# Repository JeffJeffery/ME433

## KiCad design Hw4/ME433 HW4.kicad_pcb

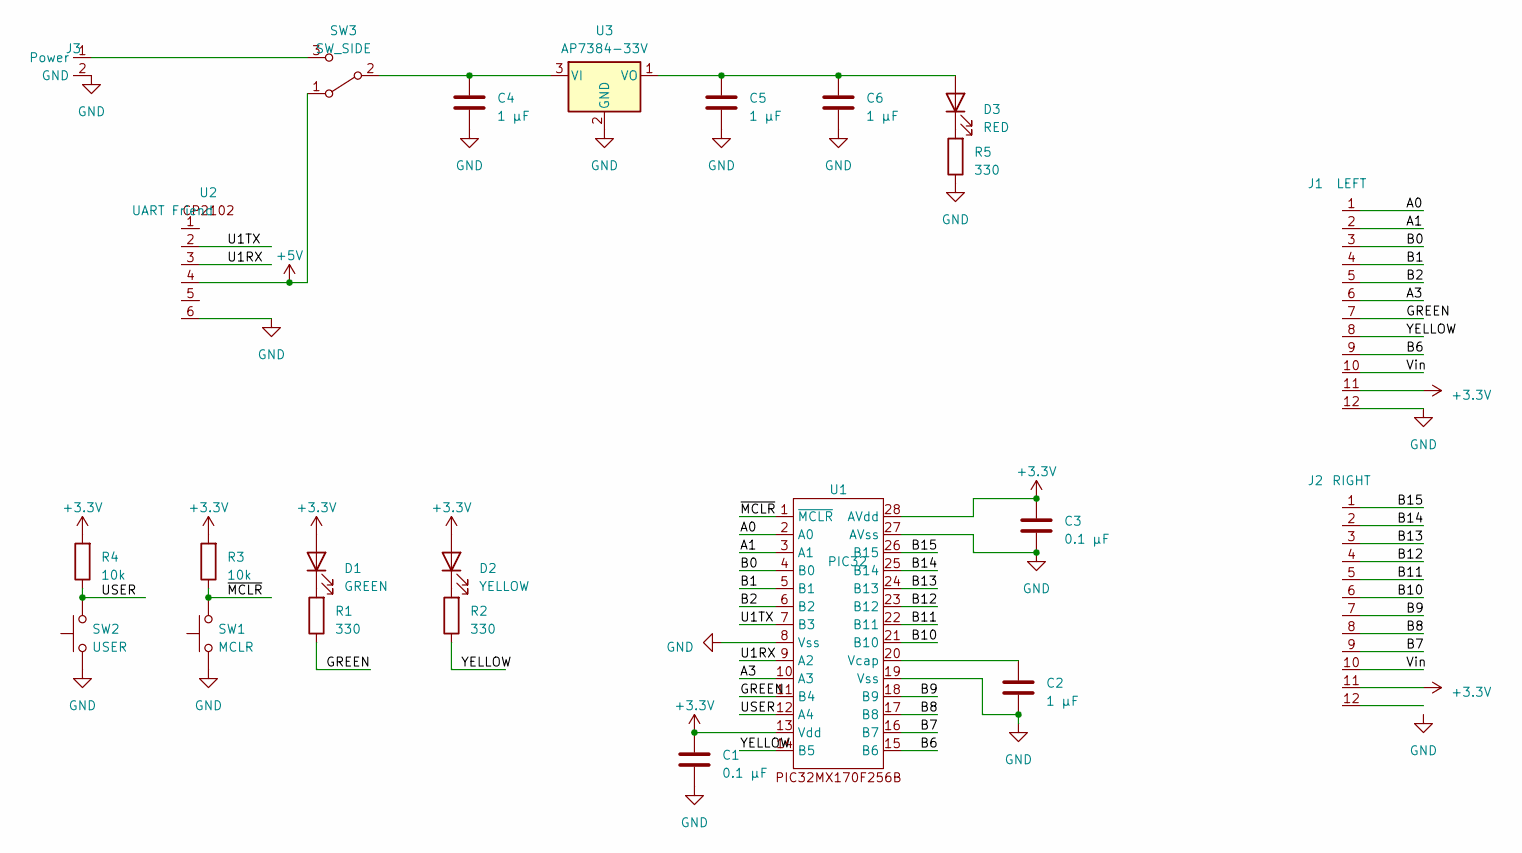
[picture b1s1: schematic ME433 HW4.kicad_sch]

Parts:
C1, C3: 0.1 µF; C_Disc_D3.4mm_W2.1mm_P2.50mm
C2, C4, C5, C6: 1 µF; C_Disc_D5.1mm_W3.2mm_P5.00mm
D1: GREEN; LED_D3.0mm
D2: YELLOW; LED_D3.0mm
D3: RED; LED_D3.0mm
J1: LEFT; PinSocket_1x12_P2.54mm_Vertical
J2: RIGHT; PinSocket_1x12_P2.54mm_Vertical
J3: PinSocket_1x02_P2.54mm_Vertical
R1, R2, R5: 330; R_Axial_DIN0207_L6.3mm_D2.5mm_P7.62mm_Horizontal
R3, R4: 10k; R_Axial_DIN0207_L6.3mm_D2.5mm_P7.62mm_Horizontal
SW1: MCLR; Button
SW2: USER; Button
SW3: SW_SIDE; SlideSwitch
U1: PIC32; DIP-28_W7.62mm_Socket
U2: UART Friend; PinSocket_1x06_P2.54mm_Vertical
U3: AP7384-33V; TO-92_Inline_Wide

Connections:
+3.3V: C1.1, C3.1, D1.2 (A), D2.2 (A), J1.11, J2.11, R3.2, R4.2, U1.13 (Vdd), U1.28 (AVdd)
+5V: SW3.1 (A), U2.4
/A0: J1.1, U1.2 (A0)
/A1: J1.2, U1.3 (A1)
/A3: J1.6, U1.10 (A3)
/B0: J1.3, U1.4 (B0)
/B1: J1.4, U1.5 (B1)
/B2: J1.5, U1.6 (B2)
/B6: J1.9, U1.15 (B6)
/B7: J2.9, U1.16 (B7)
/B8: J2.8, U1.17 (B8)
/B9: J2.7, U1.18 (B9)
/B10: J2.6, U1.21 (B10)
/B11: J2.5, U1.22 (B11)
/B12: J2.4, U1.23 (B12)
/B13: J2.3, U1.24 (B13)
/B14: J2.2, U1.25 (B14)
/B15: J2.1, U1.26 (B15)
/GREEN: J1.7, R1.1, U1.11 (B4)
/U1RX: U1.9 (A2), U2.3
/U1TX: U1.7 (B3), U2.2
/USER: R4.1, SW2.2, U1.12 (A4)
/Vin: J1.10, J2.10
/YELLOW: J1.8, R2.1, U1.14 (B5)
/~MCLR: R3.1, SW1.2, U1.1 (~MCLR)
GND: C1.2, C2.2, C3.2, C4.2, C5.2, C6.2, J1.12, J3.2 (GND), R5.1, SW1.1, SW2.1, U1.8 (Vss), U1.19 (Vss), U1.27 (AVss), U2.6, U3.2 (GND)
unnamed: D1.1 (K), R1.2
unnamed: D2.1 (K), R2.2
unnamed: C5.1, C6.1, D3.2 (A), U3.1 (VO)
unnamed: D3.1 (K), R5.2
unnamed: J3.1 (Power), SW3.3 (C)
unnamed: C4.1, SW3.2 (B), U3.3 (VI)
unnamed: C2.1, U1.20 (Vcap)

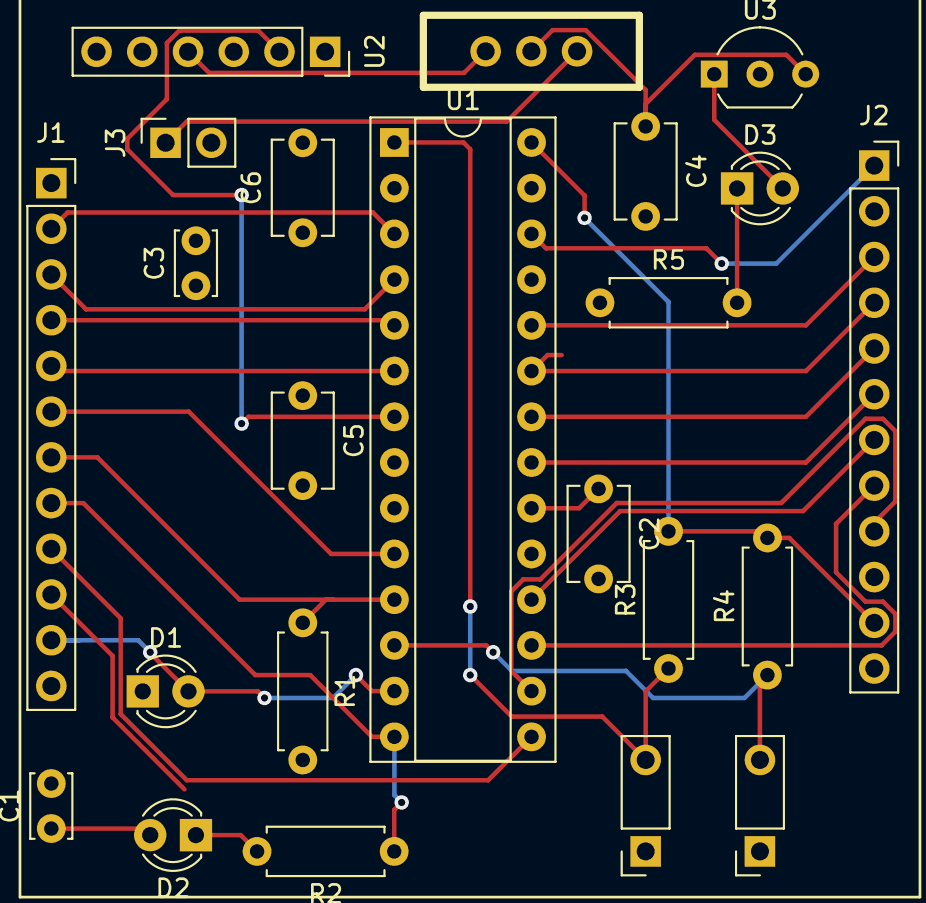
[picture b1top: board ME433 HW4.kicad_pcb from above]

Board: 2 copper layers, 23 parts (0 on the bottom side), 33 nets.

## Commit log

2023-03-28 HW1 folder commit
2023-04-04 Hw 2 Commit
2023-04-04 Fixing random files lol
2023-04-04 Bootloader change
2023-04-04 Deliverables commit
2023-04-09 Finished HW3 commit
2023-05-04 Hw 5
2023-05-16 Picture For Hw5
2023-05-16 Hw6 commit
2023-05-16 Hw7 commit
2023-05-16 FPS CHange
2023-05-17 Hw9 commit
2023-05-25 Hw10
2023-05-25 H11 commit
2023-05-30 Hw14 commit
2023-06-01 Hw13
